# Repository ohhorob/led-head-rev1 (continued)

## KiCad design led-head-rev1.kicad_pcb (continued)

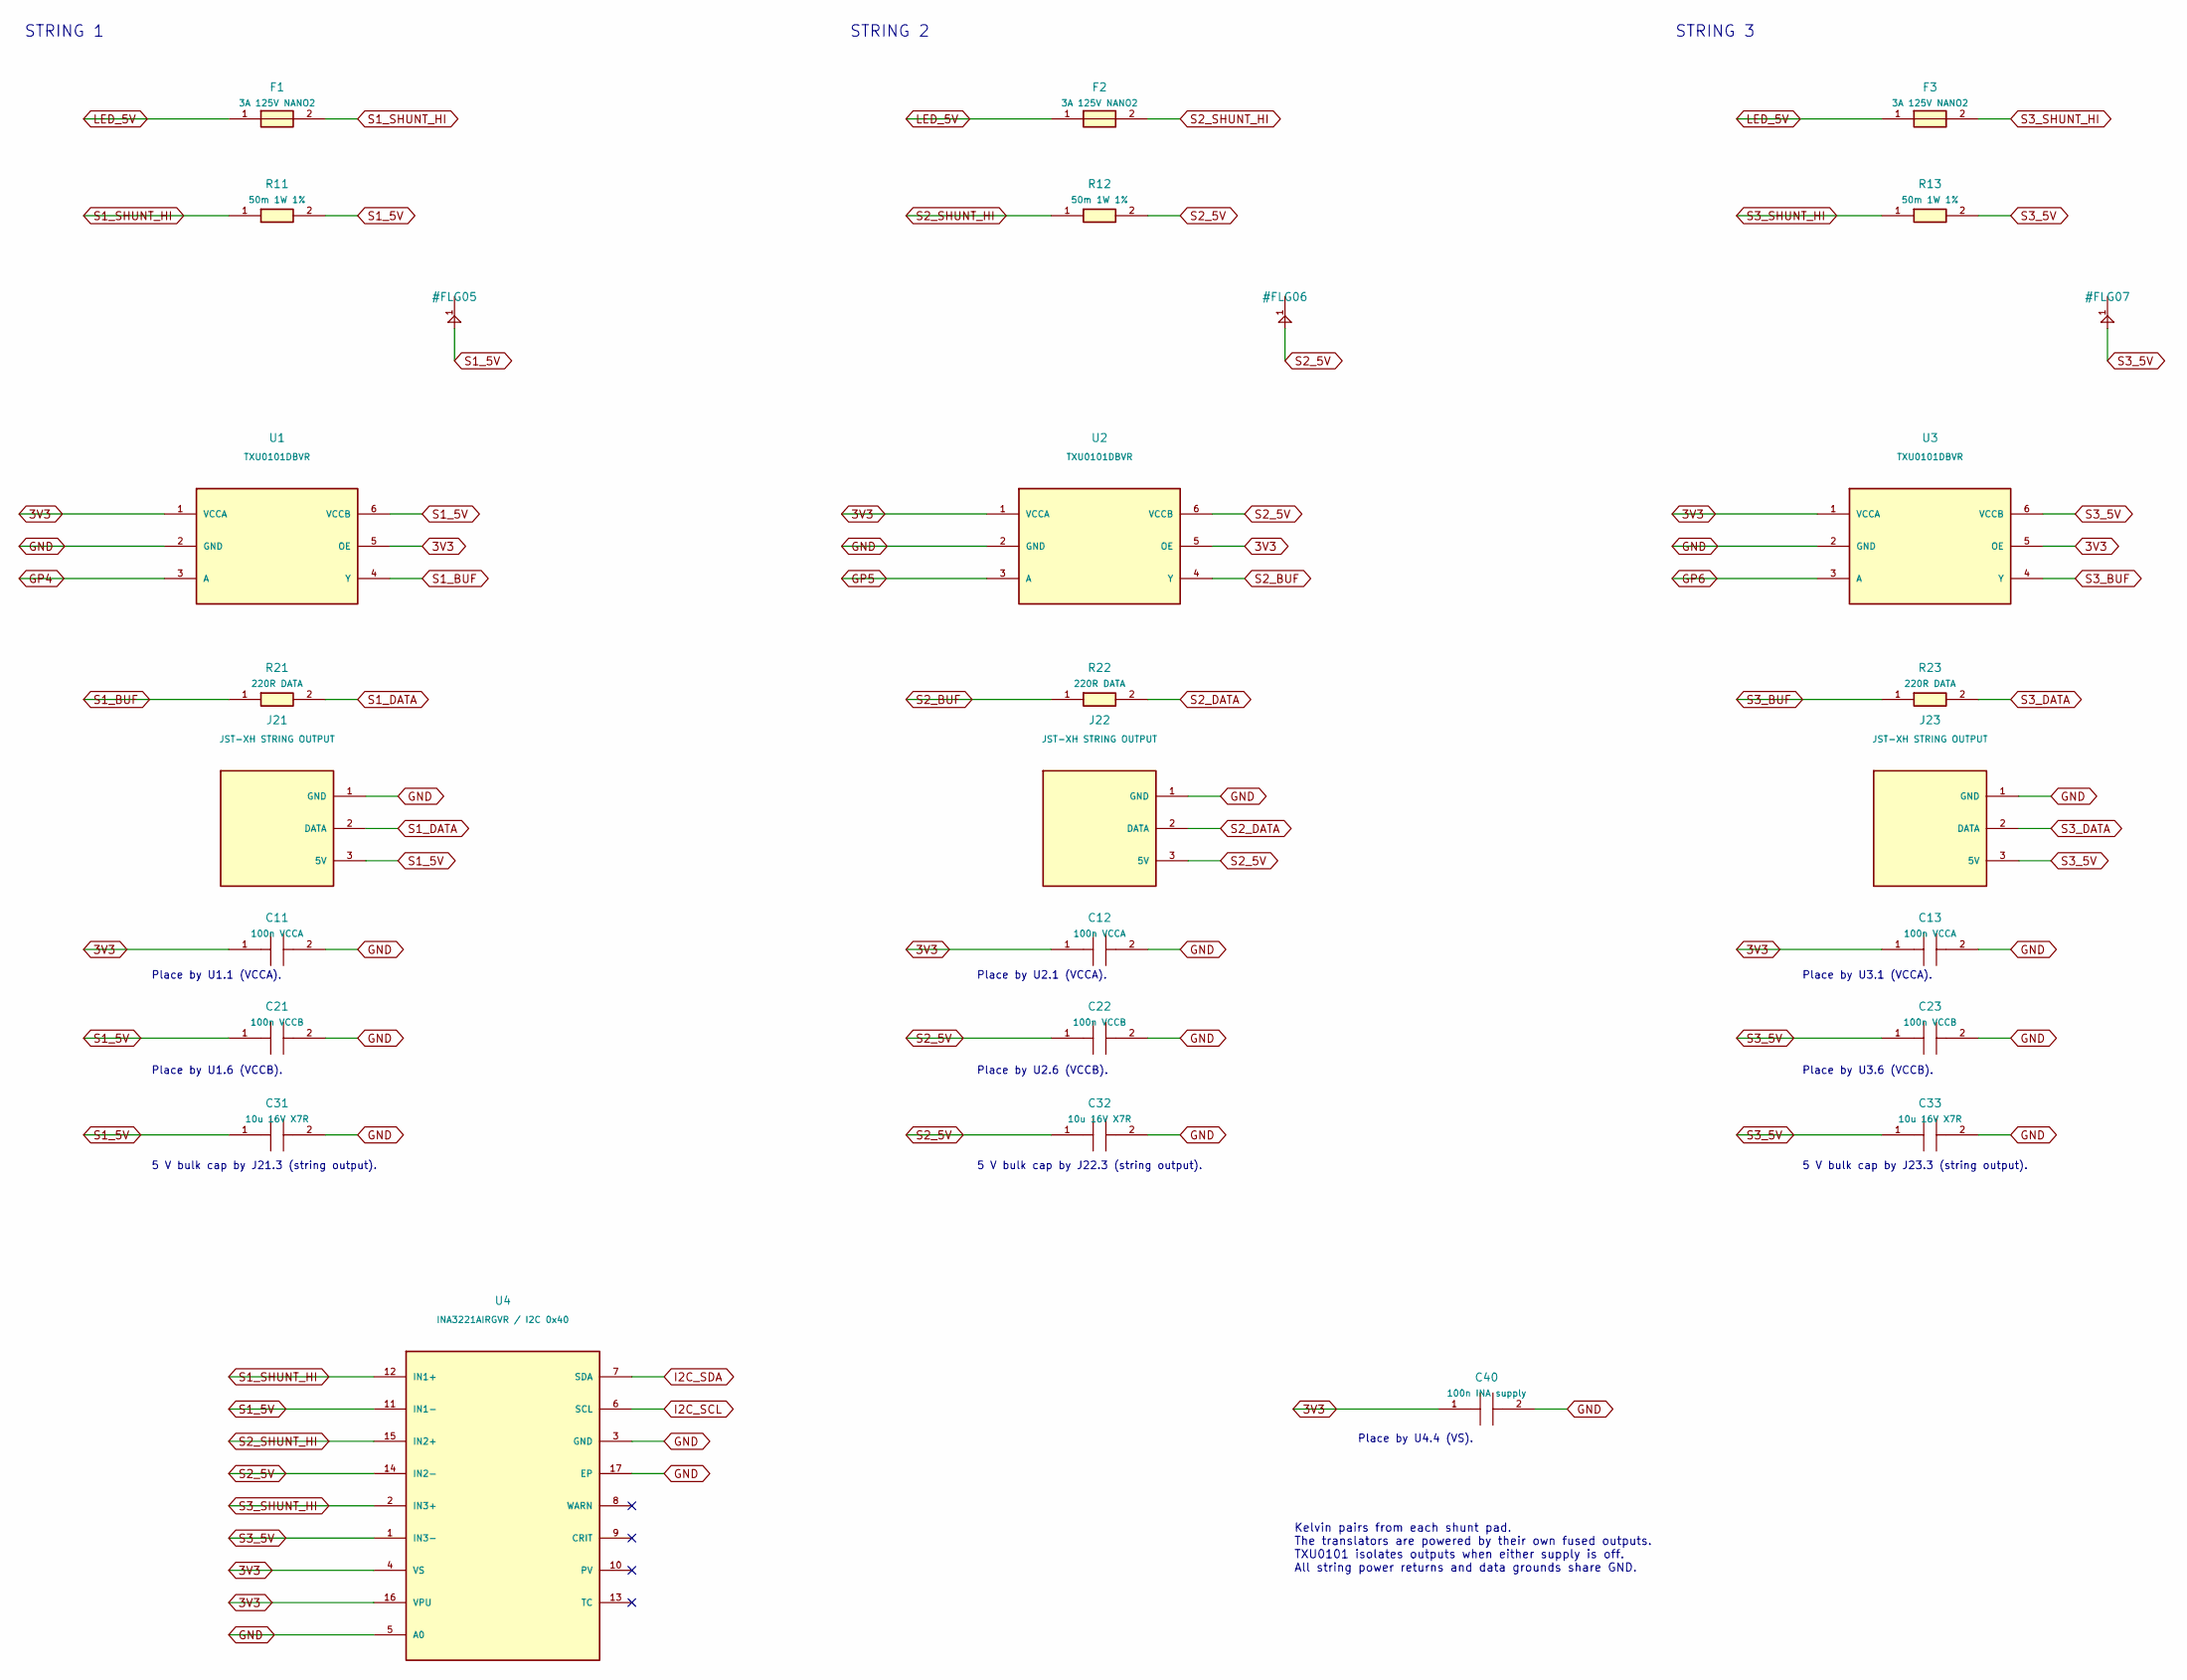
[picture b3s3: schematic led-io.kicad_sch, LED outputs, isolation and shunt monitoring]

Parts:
C11, C12, C13: 100n VCCA; C_0805_2012Metric
C21, C22, C23: 100n VCCB; C_0805_2012Metric
C31, C32, C33: 10u 16V X7R; C_1206_3216Metric
C40: 100n INA supply; C_0805_2012Metric
F1, F2, F3: 3A 125V NANO2; Fuse_Littelfuse-NANO2-451_453
J21, J22, J23: JST-XH STRING OUTPUT; JST_XH_S3B-XH-A_1x03_P2.50mm_Horizontal
R11, R12, R13: 50m 1W 1%; Vishay_WSL2512_50mR
R21, R22, R23: 220R DATA; R_0805_2012Metric
U1, U2, U3: TXU0101DBVR; SOT-23-6
U4: INA3221AIRGVR / I2C 0x40; TI_RGV0016A_Reference

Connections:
3V3: C11.1, C12.1, C13.1, C40.1, U1.1 (VCCA), U1.5 (OE), U2.1 (VCCA), U2.5 (OE), U3.1 (VCCA), U3.5 (OE), U4.4 (VS), U4.16 (VPU); also elsewhere on the board
GND: C11.2, C12.2, C13.2, C21.2, C22.2, C23.2, C31.2, C32.2, C33.2, C40.2, J21.1 (GND), J22.1 (GND), J23.1 (GND), U1.2 (GND), U2.2 (GND), U3.2 (GND), U4.3 (GND), U4.5 (A0), U4.17 (EP); also elsewhere on the board
GP4: U1.3 (A); also elsewhere on the board
GP5: U2.3 (A); also elsewhere on the board
GP6: U3.3 (A); also elsewhere on the board
I2C_SCL: U4.6 (SCL); also elsewhere on the board
I2C_SDA: U4.7 (SDA); also elsewhere on the board
LED_5V: F1.1, F2.1, F3.1; also elsewhere on the board
S1_5V: C21.1, C31.1, J21.3 (5V), R11.2, U1.6 (VCCB), U4.11 (IN1-)
S1_BUF: R21.1, U1.4 (Y)
S1_DATA: J21.2 (DATA), R21.2
S1_SHUNT_HI: F1.2, R11.1, U4.12 (IN1+)
S2_5V: C22.1, C32.1, J22.3 (5V), R12.2, U2.6 (VCCB), U4.14 (IN2-)
S2_BUF: R22.1, U2.4 (Y)
S2_DATA: J22.2 (DATA), R22.2
S2_SHUNT_HI: F2.2, R12.1, U4.15 (IN2+)
S3_5V: C23.1, C33.1, J23.3 (5V), R13.2, U3.6 (VCCB), U4.1 (IN3-)
S3_BUF: R23.1, U3.4 (Y)
S3_DATA: J23.2 (DATA), R23.2
S3_SHUNT_HI: F3.2, R13.1, U4.2 (IN3+)

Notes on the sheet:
Kelvin pairs from each shunt pad. The translators are powered by their own fused outputs. TXU0101 isolates outputs when either supply is off. All string power returns and data grounds share GND.
Place by U2.1 (VCCA).
Place by U3.1 (VCCA).
Place by U1.6 (VCCB).
5 V bulk cap by J23.3 (string output).
Place by U4.4 (VS).
5 V bulk cap by J22.3 (string output).
STRING 3
STRING 2
Place by U2.6 (VCCB).
Place by U3.6 (VCCB).
STRING 1
Place by U1.1 (VCCA).
5 V bulk cap by J21.3 (string output).

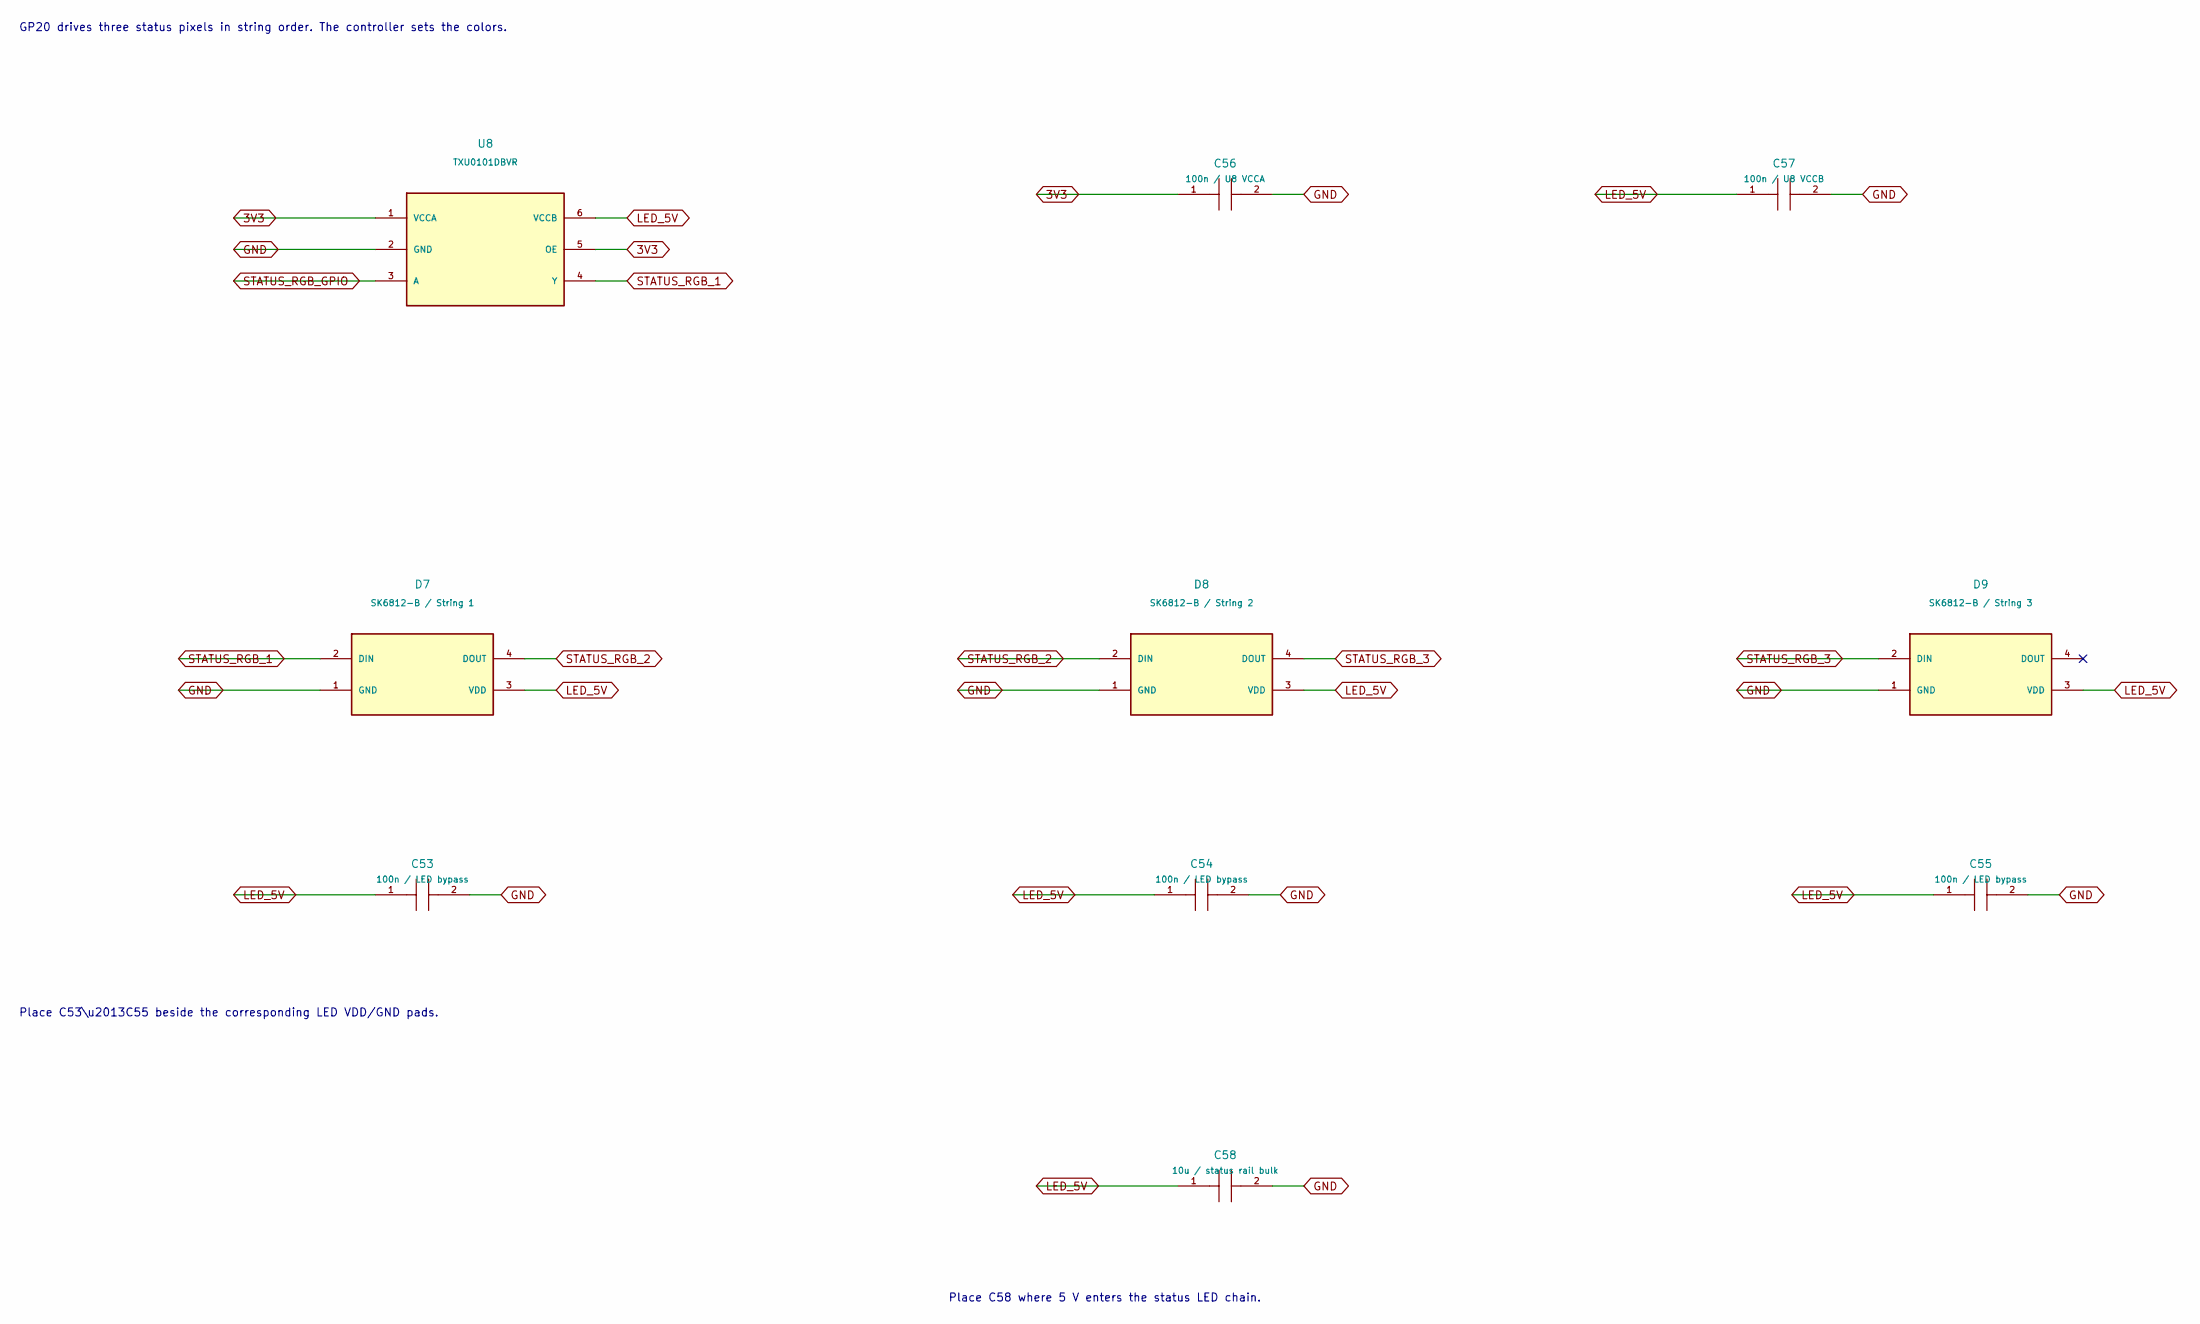
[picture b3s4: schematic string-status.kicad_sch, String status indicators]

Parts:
C53, C54, C55: 100n / LED bypass; C_0805_2012Metric
C56: 100n / U8 VCCA; C_0805_2012Metric
C57: 100n / U8 VCCB; C_0805_2012Metric
C58: 10u / status rail bulk; C_1206_3216Metric
D7: SK6812-B / String 1; LED_OPSCO_SK6812_PLCC4_5.0x5.0mm_P3.1mm
D8: SK6812-B / String 2; LED_OPSCO_SK6812_PLCC4_5.0x5.0mm_P3.1mm
D9: SK6812-B / String 3; LED_OPSCO_SK6812_PLCC4_5.0x5.0mm_P3.1mm
U8: TXU0101DBVR; SOT-23-6

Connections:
3V3: C56.1, U8.1 (VCCA), U8.5 (OE); also elsewhere on the board
GND: C53.2, C54.2, C55.2, C56.2, C57.2, C58.2, D7.1 (GND), D8.1 (GND), D9.1 (GND), U8.2 (GND); also elsewhere on the board
LED_5V: C53.1, C54.1, C55.1, C57.1, C58.1, D7.3 (VDD), D8.3 (VDD), D9.3 (VDD), U8.6 (VCCB); also elsewhere on the board
STATUS_RGB_1: D7.2 (DIN), U8.4 (Y)
STATUS_RGB_2: D7.4 (DOUT), D8.2 (DIN)
STATUS_RGB_3: D8.4 (DOUT), D9.2 (DIN)
STATUS_RGB_GPIO: U8.3 (A); also elsewhere on the board

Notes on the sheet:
Place C58 where 5 V enters the status LED chain.
GP20 drives three status pixels in string order. The controller sets the colors.
Place C53\u2013C55 beside the corresponding LED VDD/GND pads.

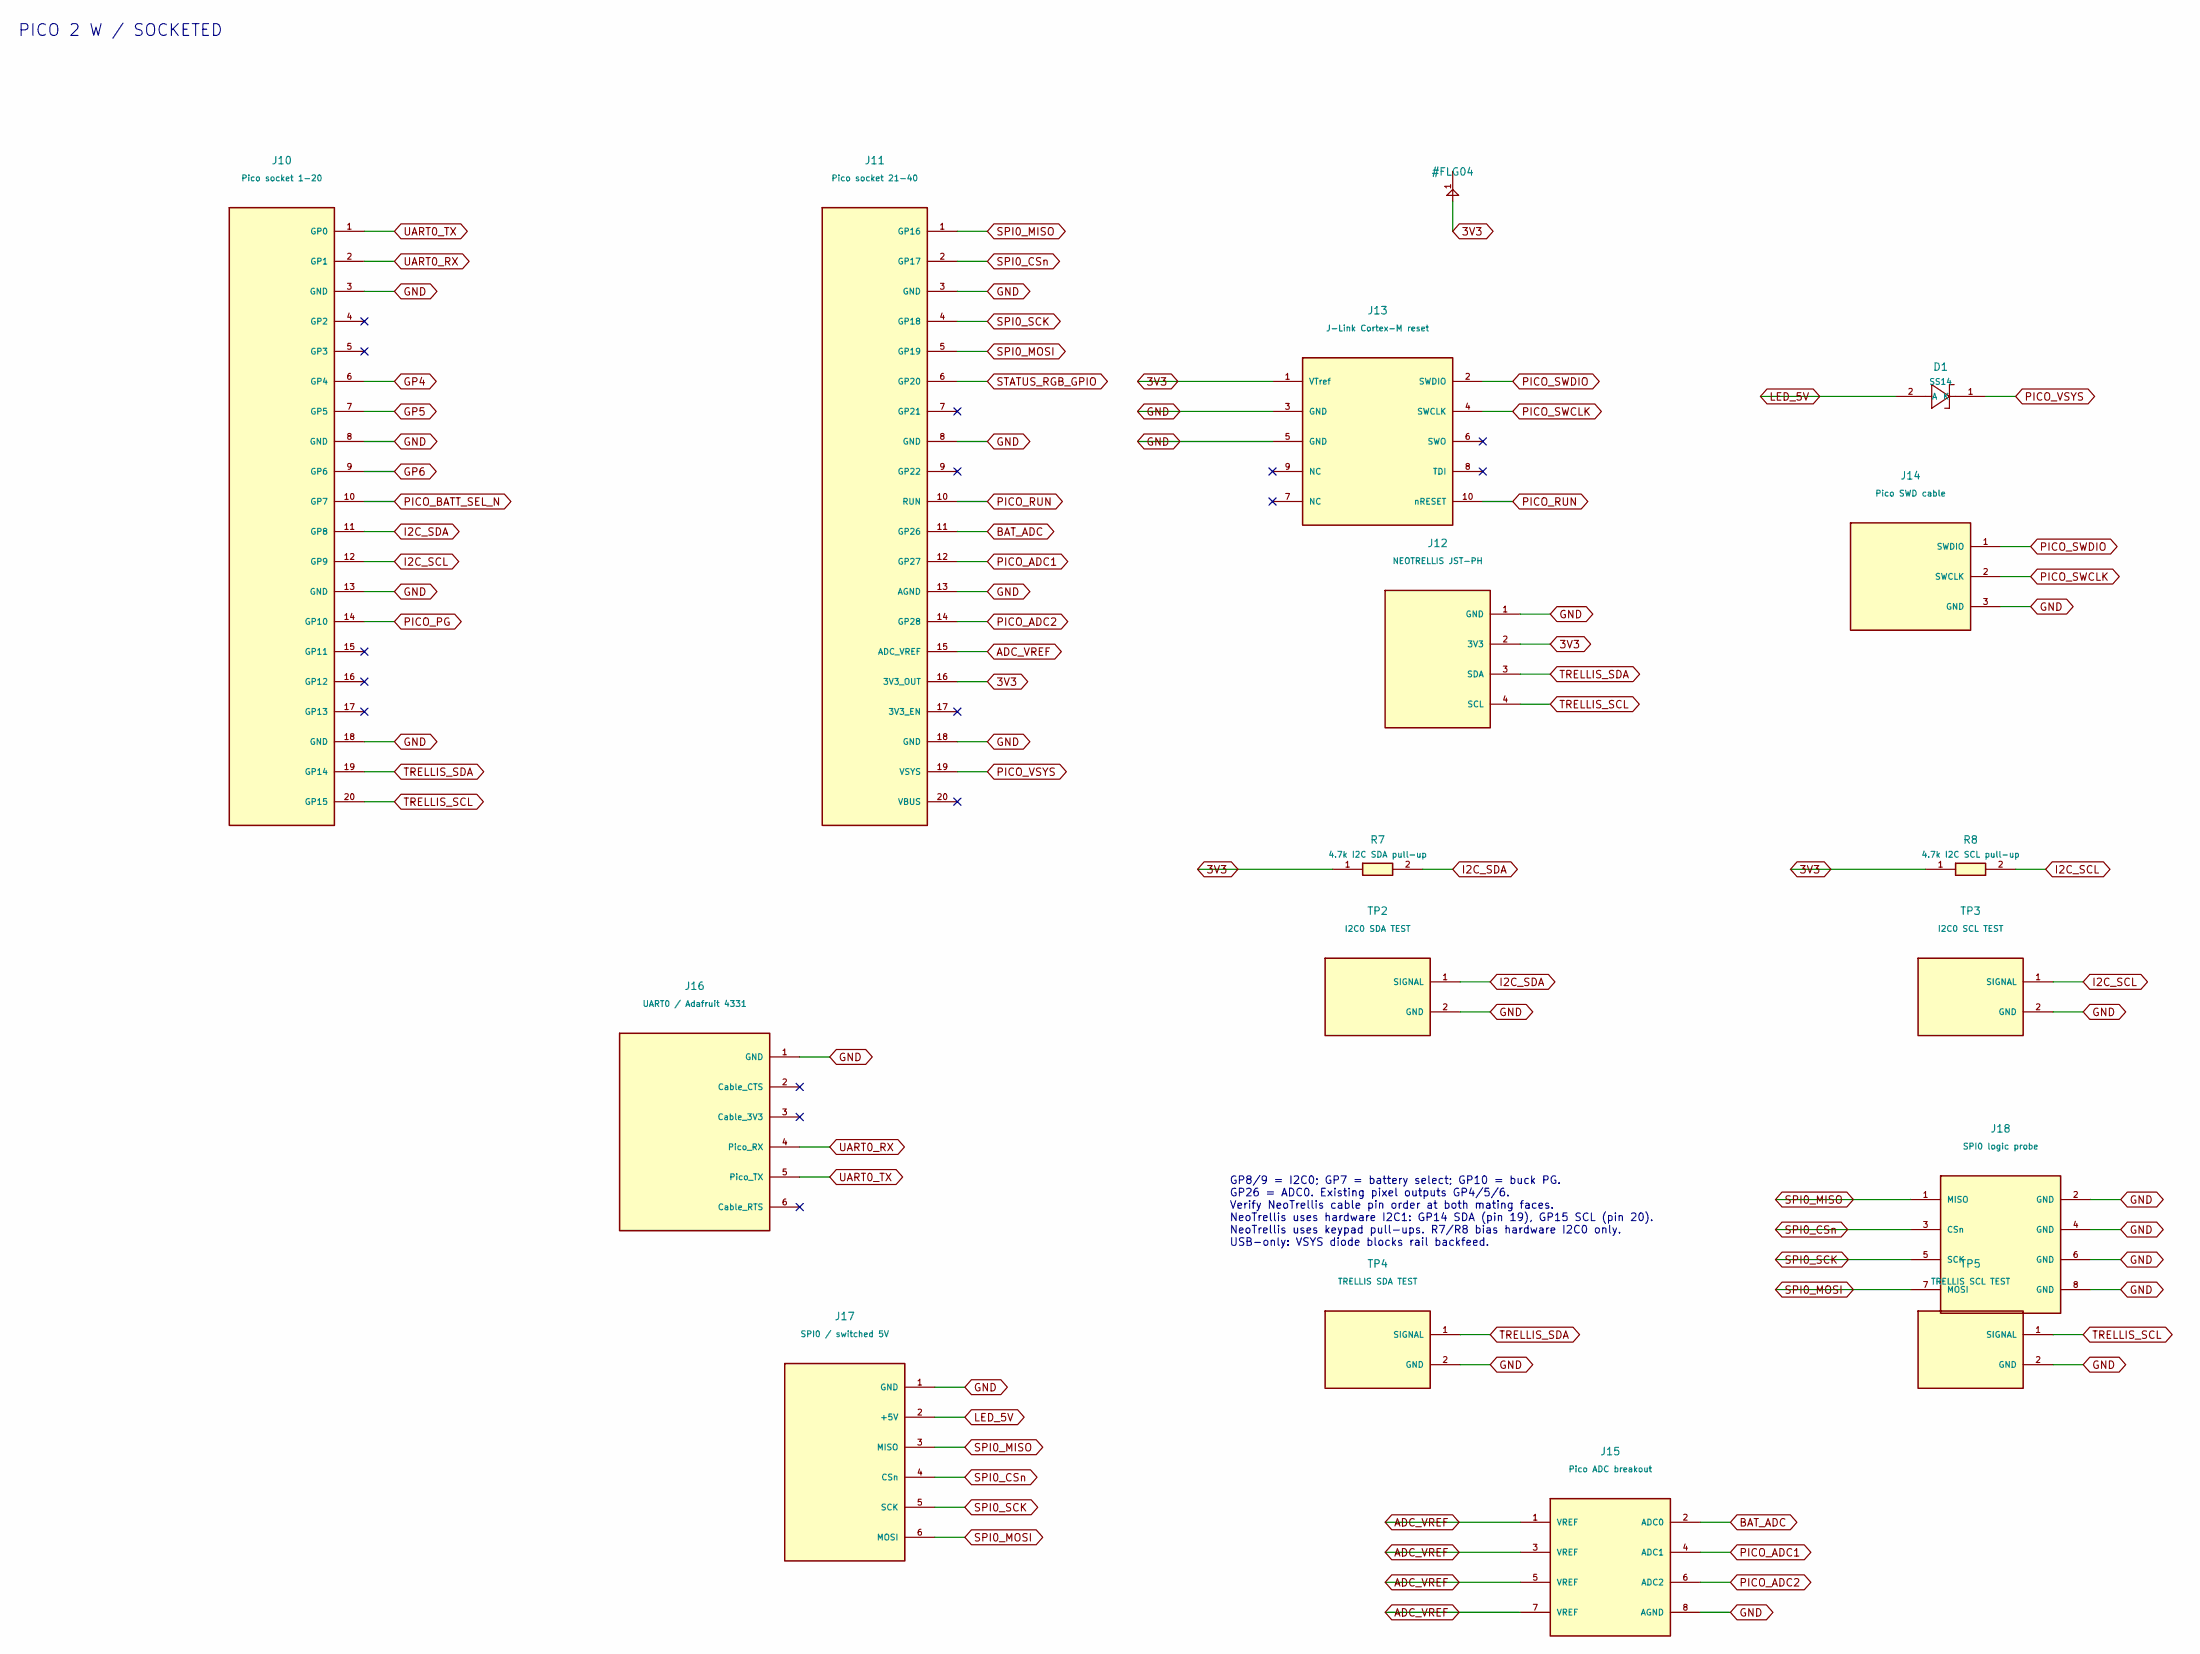
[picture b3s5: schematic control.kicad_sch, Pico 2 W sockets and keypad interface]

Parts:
D1: SS14; D_SMA
J10: Pico socket 1-20; PinSocket_1x20_P2.54mm_Vertical
J11: Pico socket 21-40; PinSocket_1x20_P2.54mm_Vertical
J12: NEOTRELLIS JST-PH; JST_PH_B4B-PH-K_1x04_P2.00mm_Vertical
J13: J-Link Cortex-M reset; Samtec_FTSH-105-01-L-DV_2x05_P1.27mm_SMT
J14: Pico SWD cable; PinHeader_1x03_P2.54mm_Vertical
J15: Pico ADC breakout; PinHeader_2x04_P2.54mm_Vertical
J16: UART0 / Adafruit 4331; PinHeader_1x06_P2.54mm_Vertical
J17: SPI0 / switched 5V; JST_PH_B6B-PH-K_1x06_P2.00mm_Vertical
J18: SPI0 logic probe; PinHeader_2x04_P2.54mm_Vertical
R7: 4.7k I2C SDA pull-up; R_0805_2012Metric
R8: 4.7k I2C SCL pull-up; R_0805_2012Metric
TP2: I2C0 SDA TEST; PinHeader_1x02_P2.54mm_Vertical
TP3: I2C0 SCL TEST; PinHeader_1x02_P2.54mm_Vertical
TP4: TRELLIS SDA TEST; PinHeader_1x02_P2.54mm_Vertical
TP5: TRELLIS SCL TEST; PinHeader_1x02_P2.54mm_Vertical

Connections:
3V3: J11.16 (3V3_OUT), J12.2 (3V3), J13.1 (VTref), R7.1, R8.1; also elsewhere on the board
ADC_VREF: J11.15 (ADC_VREF), J15.1 (VREF), J15.3 (VREF), J15.5 (VREF), J15.7 (VREF)
BAT_ADC: J11.11 (GP26), J15.2 (ADC0); also elsewhere on the board
GND: J10.3 (GND), J10.8 (GND), J10.13 (GND), J10.18 (GND), J11.3 (GND), J11.8 (GND), J11.13 (AGND), J11.18 (GND), J12.1 (GND), J13.3 (GND), J13.5 (GND), J14.3 (GND), J15.8 (AGND), J16.1 (GND), J17.1 (GND), J18.2 (GND), J18.4 (GND), J18.6 (GND), J18.8 (GND), TP2.2 (GND), TP3.2 (GND), TP4.2 (GND), TP5.2 (GND); also elsewhere on the board
GP4: J10.6 (GP4); also elsewhere on the board
GP5: J10.7 (GP5); also elsewhere on the board
GP6: J10.9 (GP6); also elsewhere on the board
I2C_SCL: J10.12 (GP9), R8.2, TP3.1 (SIGNAL); also elsewhere on the board
I2C_SDA: J10.11 (GP8), R7.2, TP2.1 (SIGNAL); also elsewhere on the board
LED_5V: D1.2 (A), J17.2 (+5V); also elsewhere on the board
PICO_ADC1: J11.12 (GP27), J15.4 (ADC1)
PICO_ADC2: J11.14 (GP28), J15.6 (ADC2)
PICO_BATT_SEL_N: J10.10 (GP7); also elsewhere on the board
PICO_PG: J10.14 (GP10); also elsewhere on the board
PICO_RUN: J11.10 (RUN), J13.10 (nRESET)
PICO_SWCLK: J13.4 (SWCLK), J14.2 (SWCLK)
PICO_SWDIO: J13.2 (SWDIO), J14.1 (SWDIO)
PICO_VSYS: D1.1 (K), J11.19 (VSYS)
SPI0_CSn: J11.2 (GP17), J17.4 (CSn), J18.3 (CSn)
SPI0_MISO: J11.1 (GP16), J17.3 (MISO), J18.1 (MISO)
SPI0_MOSI: J11.5 (GP19), J17.6 (MOSI), J18.7 (MOSI)
SPI0_SCK: J11.4 (GP18), J17.5 (SCK), J18.5 (SCK)
STATUS_RGB_GPIO: J11.6 (GP20); also elsewhere on the board
TRELLIS_SCL: J10.20 (GP15), J12.4 (SCL), TP5.1 (SIGNAL)
TRELLIS_SDA: J10.19 (GP14), J12.3 (SDA), TP4.1 (SIGNAL)
UART0_RX: J10.2 (GP1), J16.4 (Pico_RX)
UART0_TX: J10.1 (GP0), J16.5 (Pico_TX)

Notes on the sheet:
PICO 2 W / SOCKETED
GP8/9 = I2C0; GP7 = battery select; GP10 = buck PG. GP26 = ADC0. Existing pixel outputs GP4/5/6. Verify NeoTrellis cable pin order at both mating faces. NeoTrellis uses hardware I2C1: GP14 SDA (pin 19), GP15 SCL (pin 20). NeoTrellis uses keypad pull-ups. R7/R8 bias hardware I2C0 only. USB-only: VSY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

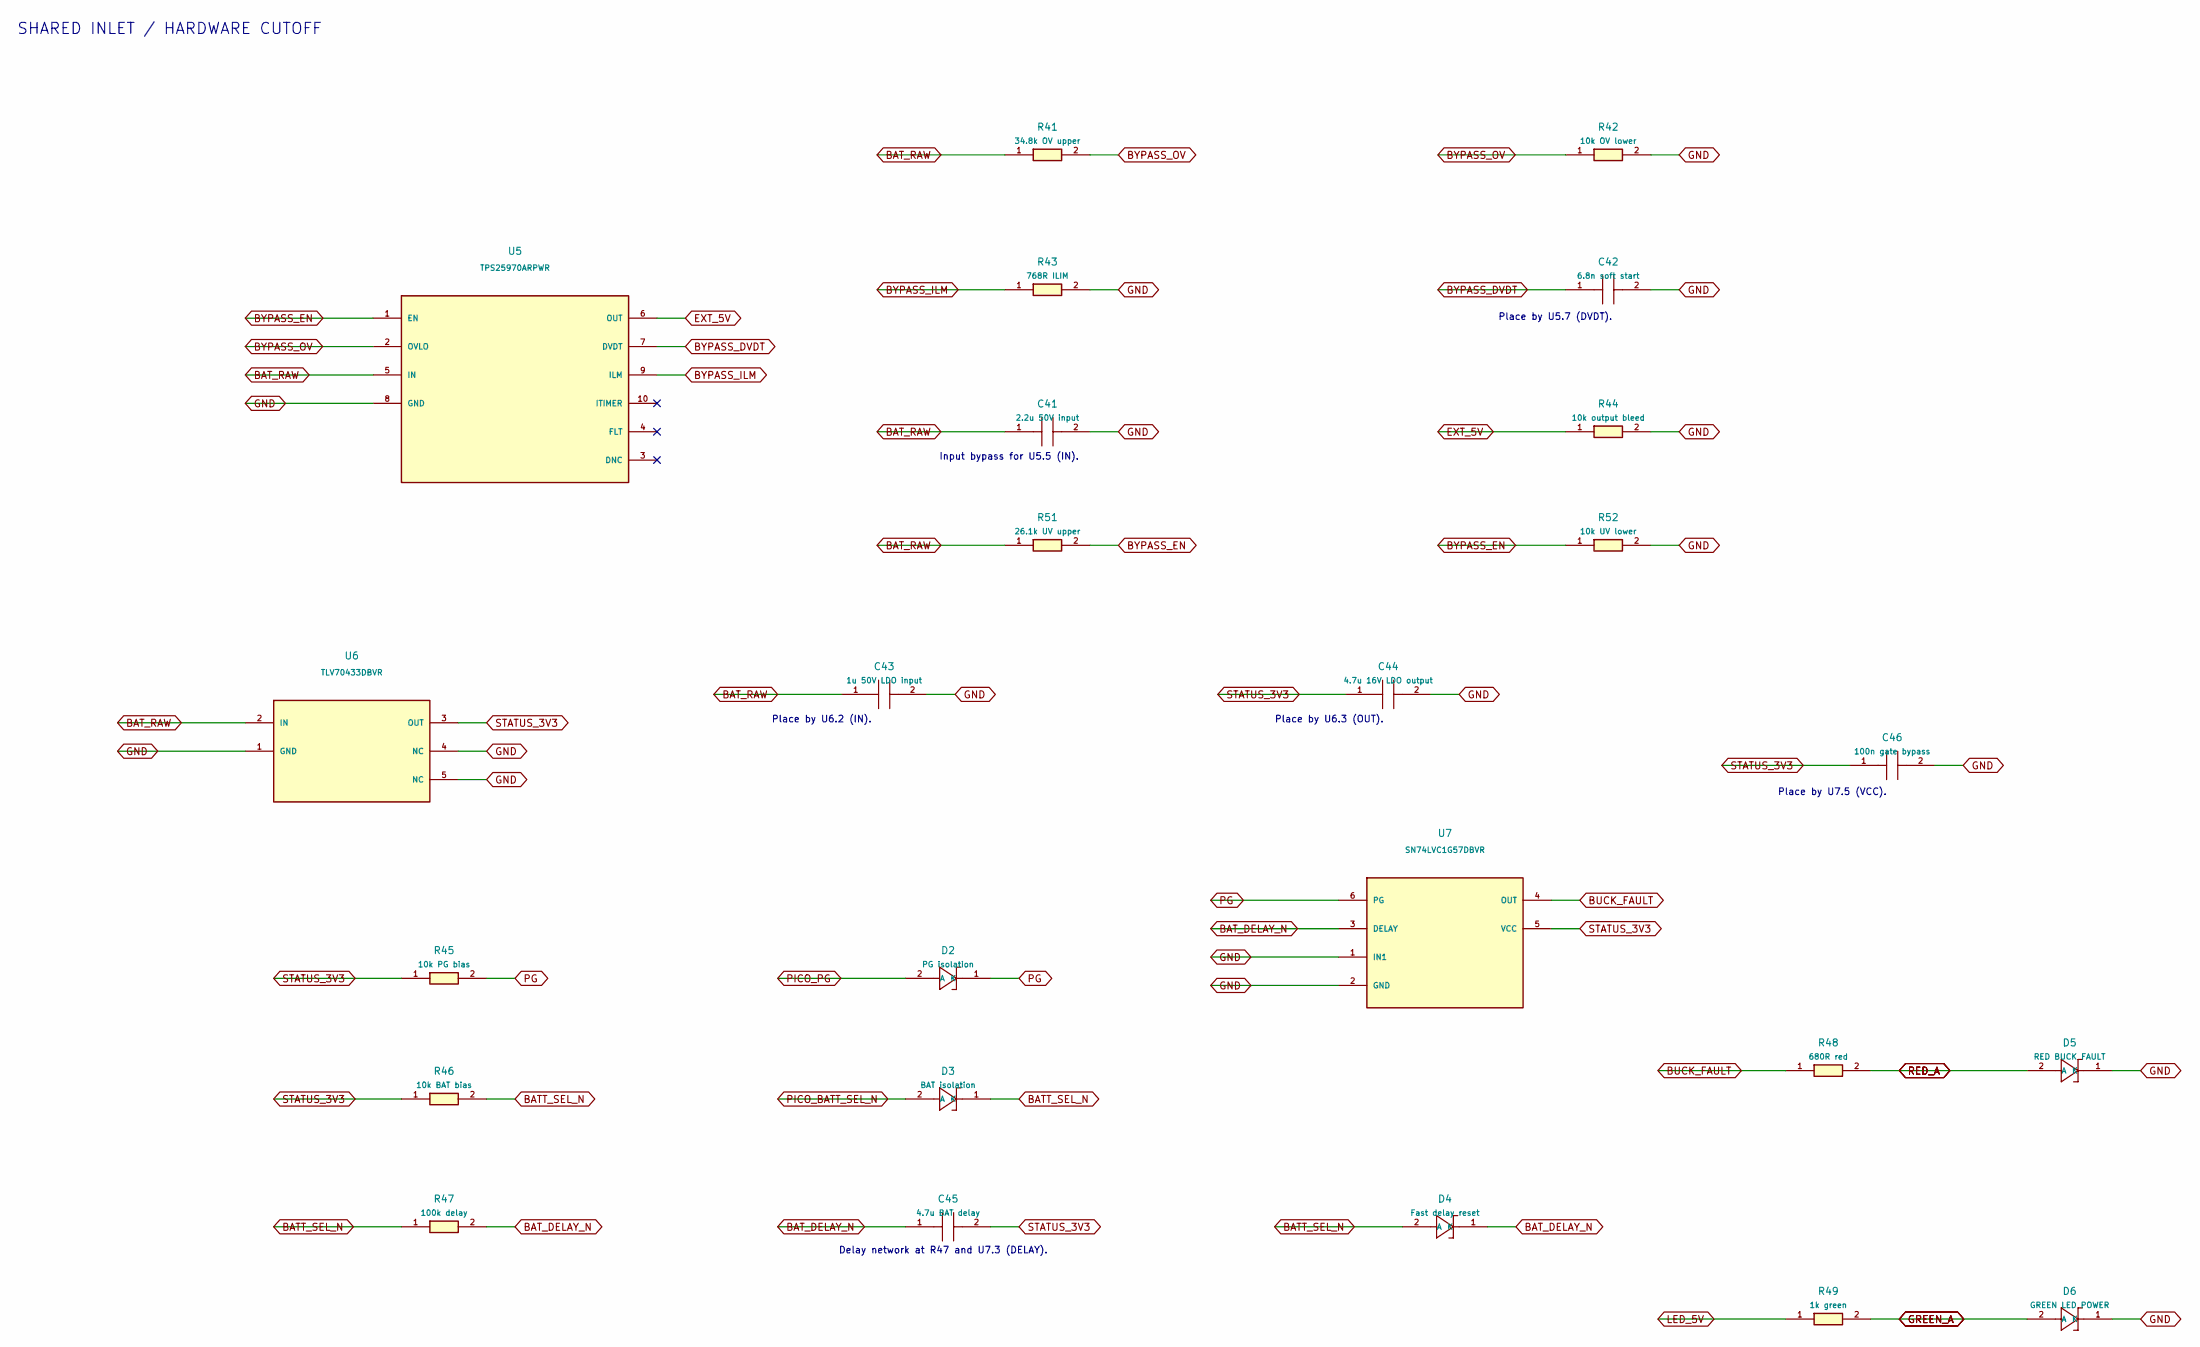
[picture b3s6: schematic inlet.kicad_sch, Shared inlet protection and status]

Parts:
C41: 2.2u 50V input; C_0805_2012Metric
C42: 6.8n soft start; C_0805_2012Metric
C43: 1u 50V LDO input; C_0805_2012Metric
C44: 4.7u 16V LDO output; C_0805_2012Metric
C45: 4.7u BAT delay; C_0805_2012Metric
C46: 100n gate bypass; C_0805_2012Metric
D2: PG isolation; D_SOD-323
D3: BAT isolation; D_SOD-323
D4: Fast delay reset; D_SOD-323
D5: RED BUCK FAULT; LED_0805_2012Metric
D6: GREEN LED POWER; LED_0805_2012Metric
R41: 34.8k OV upper; R_0805_2012Metric
R42: 10k OV lower; R_0805_2012Metric
R43: 768R ILIM; R_0805_2012Metric
R44: 10k output bleed; R_0805_2012Metric
R45: 10k PG bias; R_0805_2012Metric
R46: 10k BAT bias; R_0805_2012Metric
R47: 100k delay; R_0805_2012Metric
R48: 680R red; R_0805_2012Metric
R49: 1k green; R_0805_2012Metric
R51: 26.1k UV upper; R_0805_2012Metric
R52: 10k UV lower; R_0805_2012Metric
U5: TPS25970ARPWR; TI_RPW0010A_VQFN_HR
U6: TLV70433DBVR; SOT-23-5
U7: SN74LVC1G57DBVR; SOT-23-6

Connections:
BATT_SEL_N: D3.1 (K), D4.2 (A), R46.2, R47.1; also elsewhere on the board
BAT_DELAY_N: C45.1, D4.1 (K), R47.2, U7.3 (DELAY)
BAT_RAW: C41.1, C43.1, R41.1, R51.1, U5.5 (IN), U6.2 (IN); also elsewhere on the board
BUCK_FAULT: R48.1, U7.4 (OUT)
BYPASS_DVDT: C42.1, U5.7 (DVDT)
BYPASS_EN: R51.2, R52.1, U5.1 (EN)
BYPASS_ILM: R43.1, U5.9 (ILM)
BYPASS_OV: R41.2, R42.1, U5.2 (OVLO)
EXT_5V: R44.1, U5.6 (OUT); also elsewhere on the board
GND: C41.2, C42.2, C43.2, C44.2, C46.2, D5.1 (K), D6.1 (K), R42.2, R43.2, R44.2, R52.2, U5.8 (GND), U6.1 (GND), U6.4 (NC), U6.5 (NC), U7.1 (IN1), U7.2 (GND); also elsewhere on the board
GREEN_A: D6.2 (A), R49.2
LED_5V: R49.1; also elsewhere on the board
PG: D2.1 (K), R45.2, U7.6 (PG); also elsewhere on the board
PICO_BATT_SEL_N: D3.2 (A); also elsewhere on the board
PICO_PG: D2.2 (A); also elsewhere on the board
RED_A: D5.2 (A), R48.2
STATUS_3V3: C44.1, C45.2, C46.1, R45.1, R46.1, U6.3 (OUT), U7.5 (VCC)

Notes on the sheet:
Delay network at R47 and U7.3 (DELAY).
Place by U6.2 (IN).
Place by U7.5 (VCC).
SHARED INLET / HARDWARE CUTOFF
Input bypass for U5.5 (IN).
Place by U6.3 (OUT).
Place by U5.7 (DVDT).

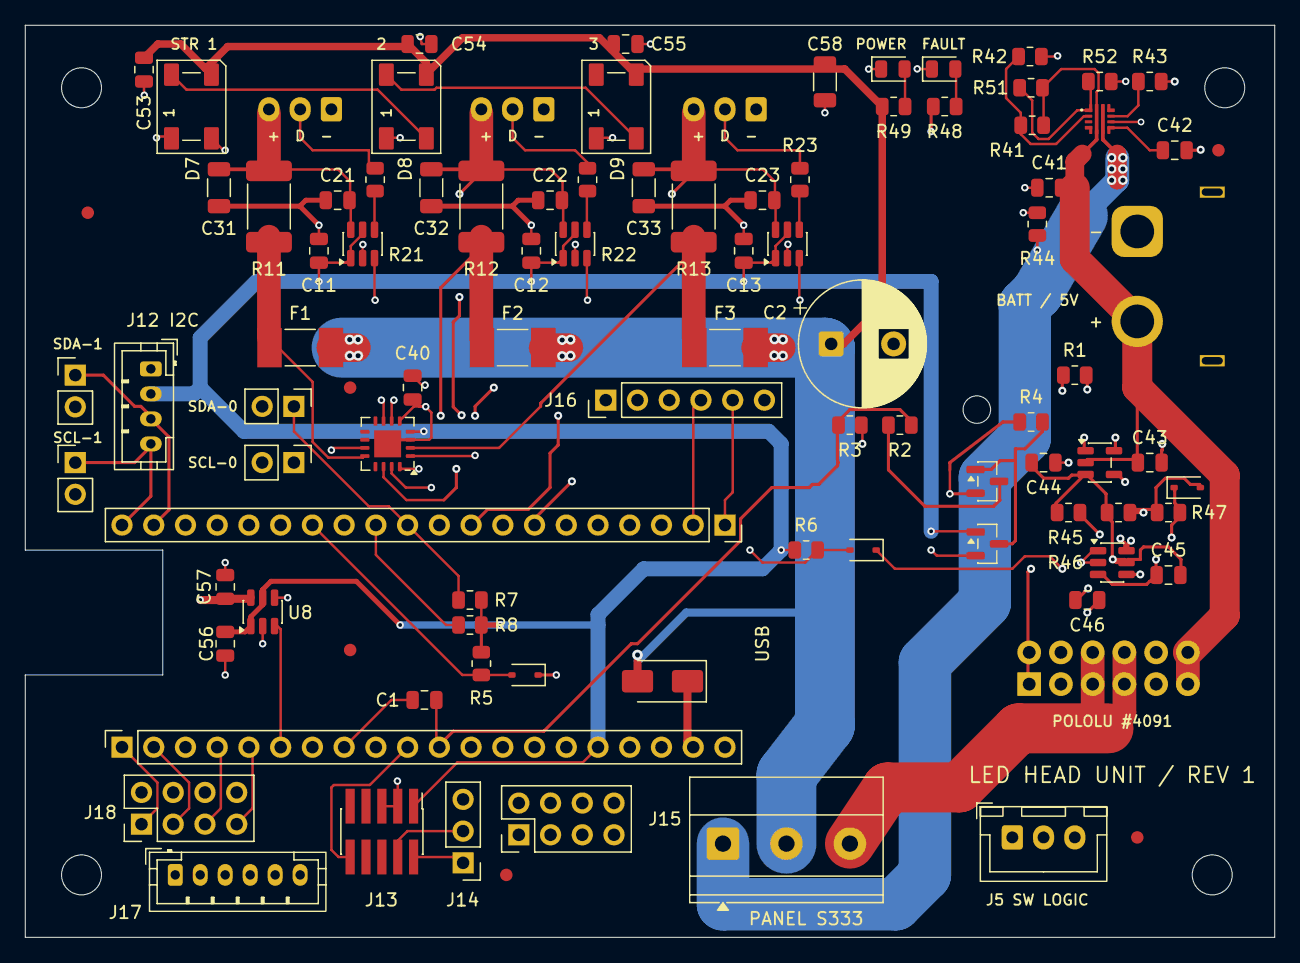
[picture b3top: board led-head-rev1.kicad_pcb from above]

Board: 4 copper layers, 100.0 x 73.0 mm, 102 parts (0 on the bottom side), 60 nets.

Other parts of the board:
FID1, FID2, FID3, FID4: Fiducial_1mm_Mask2mm
FID5, FID6: Fiducial_1mm_Mask2mm; Fiducial_1mm_Mask2mm_Local
H1, H2, H3, H4: MountingHole_3.2mm_M3
H5: MountingHole_2.2mm_M2

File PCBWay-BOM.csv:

Item #,*Designator,*Qty,Manufacturer,*Mfg Part #,Description / Value,*Package/Footprint,Type,Your Instructions / Notes
1,"C1,C11,C12,C13,C21,C22,C23,C40,C46,C53,C54,C55,C56,C57",14,KEMET,C0805C104K5RACTU,"100 nF, 50 V, X7R, +/-10% ceramic capacitor",0805 (2012 metric),SMD,Top side. Quantity is per PCB.
2,"C31,C32,C33,C58",4,Murata,GRM31CR71C106KA01L,"10 uF, 16 V, X7R, +/-10% ceramic capacitor",1206 (3216 metric),SMD,Top side. Quantity is per PCB.
3,C41,1,Murata,GRM21BR71H225KA73L,"2.2 uF, 50 V, X7R, +/-10% ceramic capacitor",0805 (2012 metric),SMD,Top side. Quantity is per PCB.
4,C42,1,KEMET,C0805C682K5RACTU,"6.8 nF, 50 V, X7R, +/-10% ceramic capacitor",0805 (2012 metric),SMD,Top side. Quantity is per PCB.
5,C43,1,Murata,GRM21BR71H105KA12L,"1 uF, 50 V, X7R, +/-10% ceramic capacitor",0805 (2012 metric),SMD,Top side. Quantity is per PCB.
6,"C44,C45",2,Murata,GRM21BR71C475KA73L,"4.7 uF, 16 V, X7R, +/-10% ceramic capacitor",0805 (2012 metric),SMD,Top side. Quantity is per PCB. Legacy MPN; quote exact part or propose an electrically equivalent 0805 X7R part for approval. Do not silently substitute.
7,D1,1,Vishay,SS14-E3/61T,"Schottky rectifier, 1 A, 40 V",SMA (DO-214AC),SMD,Top side. Quantity is per PCB.
8,"D2,D3,D4",3,Diodes Incorporated,BAT54WS-7-F,"Schottky diode, 100 mA, 30 V",SOD-323,SMD,Top side. Quantity is per PCB.
9,D5,1,Lite-On,LTST-C170KRKT,"Red LED, 0805, 20 mA test current",0805 (2012 metric),SMD,Top side. Quantity is per PCB.
10,D6,1,Lite-On,LTST-C170KGKT,"Green LED, 0805, 20 mA test current",0805 (2012 metric),SMD,Top side. Quantity is per PCB.
11,"D7,D8,D9",3,OPSCO,SK6812-B-012,"Addressable RGB LED, 5 V, 12 mA/channel, 24-bit, 800 kbit/s",5050 PLCC-4; 5.0 x 5.0 mm body,SMD,"Top side. Quantity is per PCB. Exact OPSCO black-body variant. Pin 1 GND, 2 DIN, 3 VDD, 4 DOUT. SAP 10201T6812A50034A0. Confirm footprint/orientation before assembly. Do not substitute generic SK6812 pinout."
12,"F1,F2,F3",3,Littelfuse,0451003.MRL,"3 A, 125 V fast-acting NANO2 fuse",NANO2 451; 6.10 x 2.69 mm,SMD,Top side. Quantity is per PCB.
13,J13,1,Samtec,FTSH-105-01-L-DV-TR,"10-pin male header, 2 x 5, 1.27 mm pitch, vertical SMT, all pins fitted",FTSH-105-01-L-DV SMT,SMD,Top side. Quantity is per PCB.
14,Q1,1,Nexperia,"BSS84,215","P-channel MOSFET, -50 V, -130 mA",SOT-23,SMD,Top side. Quantity is per PCB.
15,Q2,1,Nexperia,"2N7002,215","N-channel MOSFET, 60 V, 300 mA",SOT-23,SMD,Top side. Quantity is per PCB.
16,R1,1,YAGEO,RC0805FR-0713K7L,"13.7 kohm, +/-1%, 0.125 W thick-film resistor",0805 (2012 metric),SMD,Top side. Quantity is per PCB.
17,"R11,R12,R13",3,Vishay,WSL2512R0500FEA,"0.050 ohm, 1 W, +/-1% current-sense resistor",2512,SMD,Top side. Quantity is per PCB.
18,"R2,R4,R47",3,YAGEO,RC0805FR-07100KL,"100 kohm, +/-1%, 0.125 W thick-film resistor",0805 (2012 metric),SMD,Top side. Quantity is per PCB.
19,"R21,R22,R23",3,YAGEO,RC0805FR-07220RL,"220 ohm, +/-1%, 0.125 W thick-film resistor",0805 (2012 metric),SMD,Top side. Quantity is per PCB.
20,"R3,R5,R6,R44,R45,R46,R52",7,YAGEO,RC0805FR-0710KL,"10 kohm, +/-1%, 0.125 W thick-film resistor",0805 (2012 metric),SMD,Top side. Quantity is per PCB.
21,R41,1,YAGEO,RT0805BRD0734K8L,"34.8 kohm, +/-0.1%, 0.125 W thin-film resistor",0805 (2012 metric),SMD,Top side. Quantity is per PCB.
22,R42,1,YAGEO,RT0805BRD0710KL,"10 kohm, +/-0.1%, 0.125 W thin-film resistor",0805 (2012 metric),SMD,Top side. Quantity is per PCB.
23,R43,1,YAGEO,RC0805FR-07768RL,"768 ohm, +/-1%, 0.125 W thick-film resistor",0805 (2012 metric),SMD,Top side. Quantity is per PCB.
24,R48,1,YAGEO,RC0805FR-07680RL,"680 ohm, +/-1%, 0.125 W thick-film resistor",0805 (2012 metric),SMD,Top side. Quantity is per PCB.
25,R49,1,YAGEO,RC0805FR-071KL,"1 kohm, +/-1%, 0.125 W thick-film resistor",0805 (2012 metric),SMD,Top side. Quantity is per PCB.
26,R51,1,YAGEO,RC0805FR-0726K1L,"26.1 kohm, +/-1%, 0.125 W thick-film resistor",0805 (2012 metric),SMD,Top side. Quantity is per PCB.
27,"R7,R8",2,YAGEO,RC0805FR-074K7L,"4.7 kohm, +/-1%, 0.125 W thick-film resistor",0805 (2012 metric),SMD,Top side. Quantity is per PCB.
28,"U1,U2,U3,U8",4,Texas Instruments,TXU0101DBVR,Single-bit noninverting voltage-level translator; VCCA/VCCB 1.1-5.5 V,SOT-23-6 (DBV),SMD,Top side. Quantity is per PCB.
29,U4,1,Texas Instruments,INA3221AIRGVR,"Triple-channel shunt/bus voltage monitor, I2C, address 0x40","VQFN-16 with exposed pad, 4 x 4 mm (RGV)",SMD,Top side. Quantity is per PCB.
30,U5,1,Texas Instruments,TPS25970ARPWR,"2.7-23 V, 7 A eFuse, adjustable current limit","VQFN-HR-10, 2 x 2 mm (RPW)",SMD,Top side. Quantity is per PCB. Exact A variant; verify availability and RPW land pattern.
31,U6,1,Texas Instruments,TLV70433DBVR,"3.3 V fixed-output LDO, 150 mA, input up to 24 V",SOT-23-5 (DBV),SMD,Top side. Quantity is per PCB.
32,U7,1,Texas Instruments,SN74LVC1G57DBVR,"Configurable multifunction logic gate, 1.65-5.5 V",SOT-23-6 (DBV),SMD,Top side. Quantity is per PCB.
